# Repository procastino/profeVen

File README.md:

# profeVen
## What is this?
A little Arduino indicator for computer science class management. It must be placed on a visible spot on the student's table. It has an RGB LED and two pushbuttons, start and reset. When you press button start, led lights, indicating that the student needs the teacher (profe) to come (ven) and help him/her. Every while (1 minute by default), if the teacher has not attended the student demand, light will change color according to the sequence purple - cyan - blue - yellow - red, so that the teacher knows who has been waiting the most. When the light gets red, it stays there. When teacher solves the student's problem, presses reset button to turn light off. If the student has finished his work and wants to let the teacher know that he is ready to go on, he can long press the start button and a green light will start to fade out and in.
## (Not so) technicals
This device is controlled by an atTiny85, and powered by an USB connection. It has a custom PCB designed in KiCad and it's enclosure is designed in the openSCad files. The "lid" part must be printed with transparent or translucid plastic.
Programming is written in Arduino, surely it's not great code, but it gets the job done.
## Disclaimer
It is a quite overengineered solution for managing classrooms, you can obviously find simpler ways of dealing with your students doubts. But I teach design and technology, so... what did you expect?

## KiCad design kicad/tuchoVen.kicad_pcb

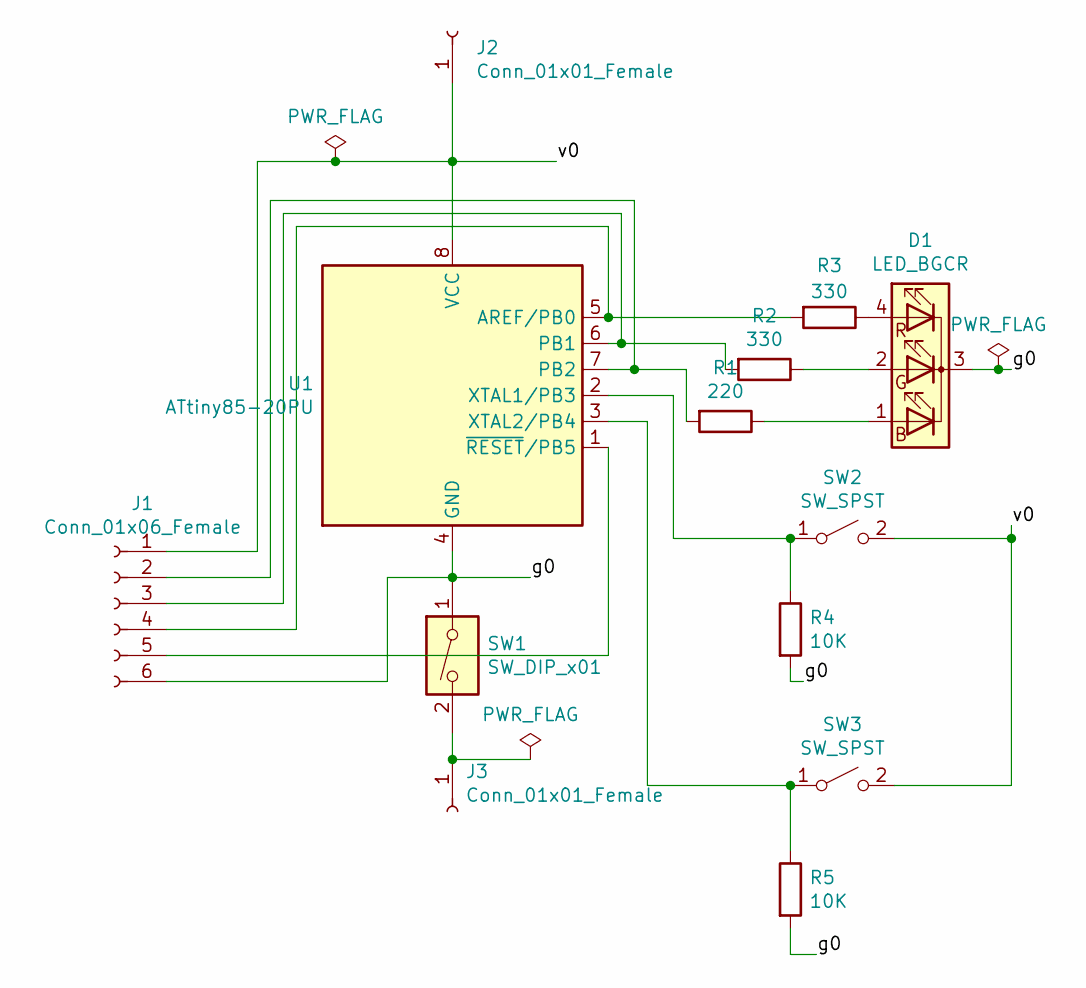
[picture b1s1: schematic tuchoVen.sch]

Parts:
D1: LED_BGCR; LED_D5.0mm-4_RGB
J1: Conn_01x06_Female; PinHeader_1x06_P2.54mm_Horizontal
J2, J3: Conn_01x01_Female; SolderWire-0.25sqmm_1x01_D0.65mm_OD1.7mm_Relief
R1: 220; R_Axial_DIN0207_L6.3mm_D2.5mm_P7.62mm_Horizontal
R2, R3: 330; R_Axial_DIN0207_L6.3mm_D2.5mm_P7.62mm_Horizontal
R4, R5: 10K; R_Axial_DIN0207_L6.3mm_D2.5mm_P7.62mm_Horizontal
SW1: SW_DIP_x01; SW_CuK_OS102011MA1QN1_SPDT_Angled
SW2, SW3: SW_SPST; SW_PUSH_6mm
U1: ATtiny85-20PU; DIP-8_W7.62mm

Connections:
/g0: D1.3 (K), J1.6, R4.2, R5.2, SW1.1, U1.4 (GND)
/v0: J1.1, J2.1, SW2.2 (B), SW3.2 (B), U1.8 (VCC)
unnamed: D1.1 (BA), R1.1
unnamed: D1.2 (GA), R2.1
unnamed: D1.4 (RA), R3.1
unnamed: J1.2, R1.2, U1.7 (PB2)
unnamed: J1.3, R2.2, U1.6 (PB1)
unnamed: J1.4, R3.2, U1.5 (AREF/PB0)
unnamed: J1.5, U1.1 (~RESET~/PB5)
unnamed: J3.1, SW1.2
unnamed: R4.1, SW2.1 (A), U1.2 (XTAL1/PB3)
unnamed: R5.1, SW3.1 (A), U1.3 (XTAL2/PB4)

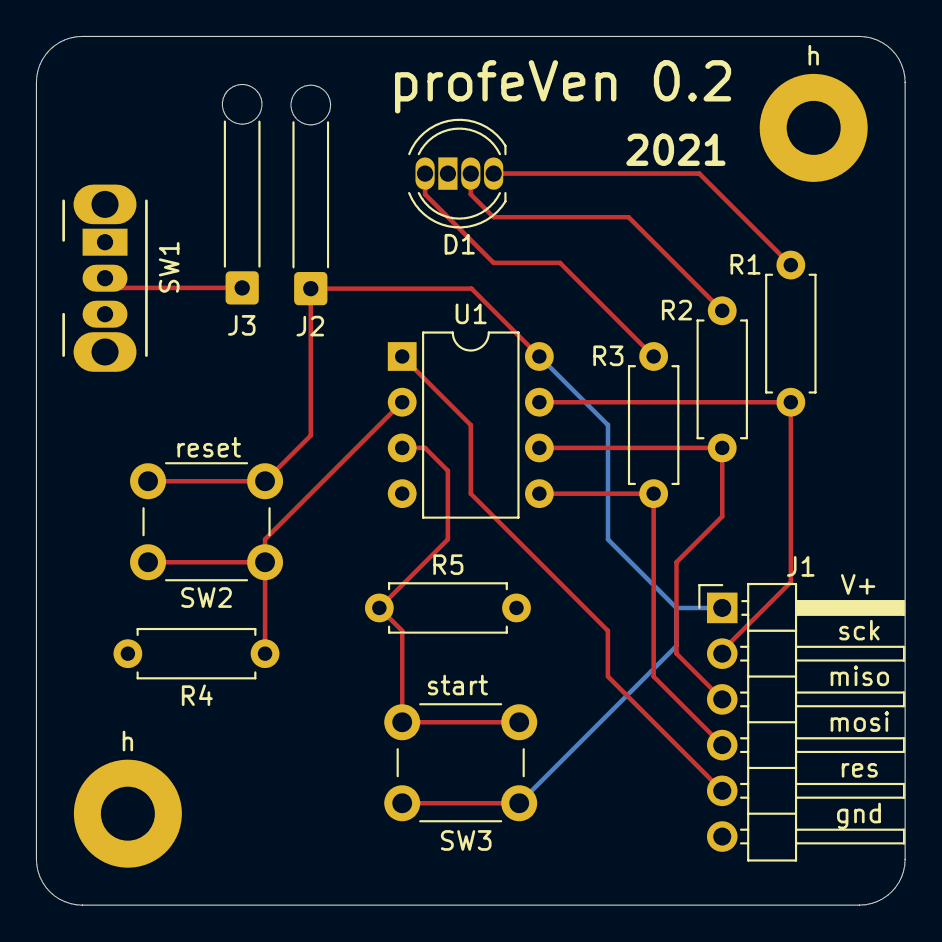
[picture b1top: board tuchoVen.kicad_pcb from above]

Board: 2 copper layers, 48.3 x 48.3 mm, 15 parts (0 on the bottom side), 12 nets.

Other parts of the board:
h: MountingHole_3mm_Pad
h#2: MountingHole_3mm_Pad

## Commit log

2021-12-27 added boards
2022-07-12 comments added
2022-07-20 pulido
2022-07-25 beautified
2022-08-12 description added
